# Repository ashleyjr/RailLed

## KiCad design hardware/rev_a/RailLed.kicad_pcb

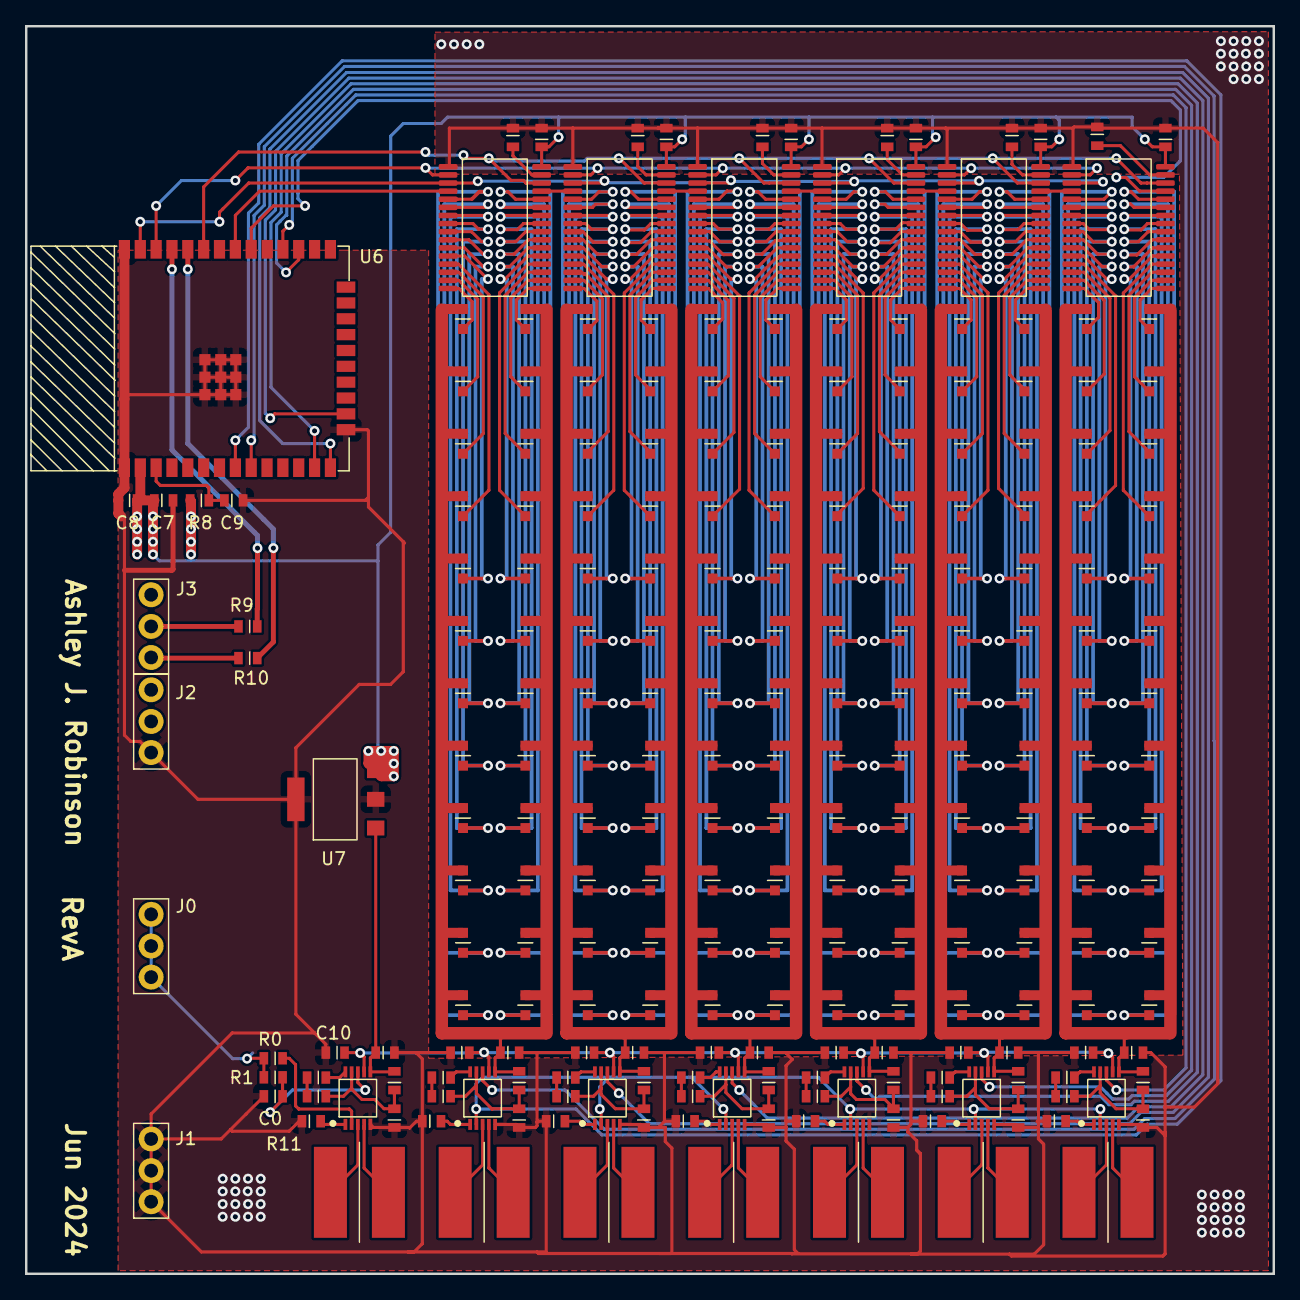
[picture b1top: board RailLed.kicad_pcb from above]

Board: 2 copper layers, 100.0 x 100.0 mm, 240 parts (0 on the bottom side), 226 nets.

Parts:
C0, C1, C2, C3, C4, C5, C6, C7, C8, C9, C10, C11, C12, C13, C14, C15, C16, C17, C18, C19, C20, C21, C22, C23, C24, C25, C26, C27, C28, C29, C30: CAP_0603; 0603
D0, D1, D2, D3, D4, D5, D6, D7, D8, D9, D10, D11, D12, D13, D14, D15, D16, D17, D18, D19, D20, D21, D22, D23, D24, D25, D26, D27, D28, D29, D30, D31, D32, D33, D34, D35, D36, D37, D38, D39, D40, D41, D42, D43, D44, D45, D46, D47, D48, D49, D50, D51, D52, D53, D54, D55, D56, D57, D58, D59, D60, D61, D62, D63, D64, D65, D66, D67, D68, D69, D70, D71, D72, D73, D74, D75, D76, D77, D78, D79, D80, D81, D82, D83, D84, D85, D86, D87, D88, D89, D90, D91, D92, D93, D94, D95, D96, D97, D98, D99, D100, D101, D102, D103, D104, D105, D106, D107, D108, D109, D110, D111, D112, D113, D114, D115, D116, D117, D118, D119, D120, D121, D122, D123, D124, D125, D126, D127, D128, D129, D130, D131, D132, D133, D134, D135, D136, D137, D138, D139, D140, D141, D142, D143: 150060GS75000
J0, J1, J2, J3: XG8V-0331
L0, L1, L2, L3, L4, L5, L6: CDRH6D38NP-100NC
R0, R1, R2, R3, R4, R5, R6, R7, R8, R9, R10, R11, R12, R13, R14, R15, R16, R17, R18, R19, R20, R21, R22, R23, R24, R25, R26, R27, R28, R29, R30, R31, R32, R33, R34, R35, R36, R37, R38: RES_0603; 0603
U0, U1, U2, U3, U4, U5: TLC5947DAP
U6: ESP32-WROOM-32D
U7: MIC5239-3.3YS
U8, U9, U10, U11, U12, U13, U14: LTC3440EMS#PBF

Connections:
+3V3: C1.1, C2.1, C3.1, C4.1, C5.1, C6.1, C7.1, C8.1, R8.2, U0.32 (VCC), U1.32 (VCC), U2.32 (VCC), U3.32 (VCC), U4.32 (VCC), U5.32 (VCC), U6.2 (3V3), U7.3 (OUT)
+BATT: C10.1, C13.1, C16.1, C19.1, C22.1, C25.1, C28.1, J0.1, J0.2, J0.3, R0.2, R1.2, U8.7 (Vin), U9.7 (Vin), U10.7 (Vin), U11.7 (Vin), U12.7 (Vin), U13.7 (Vin), U14.7 (Vin)
/BANK1/BLANK: U0.2 (BLANK), U1.2 (BLANK), U2.2 (BLANK), U3.2 (BLANK), U4.2 (BLANK), U5.2 (BLANK), U6.36 (IO22)
/BANK1/SCLK: U0.3 (SCLK), U1.3 (SCLK), U2.3 (SCLK), U3.3 (SCLK), U4.3 (SCLK), U5.3 (SCLK), U6.37 (IO23)
/BANK1/SIN: U0.4 (SIN), U6.31 (IO19)
/BANK1/SOUT: U0.29 (SOUT), U1.4 (SIN)
/BANK1/VLED: C15.1, D0.2, D1.2, D2.2, D3.2, D4.2, D5.2, D6.2, D7.2, D8.2, D9.2, D10.2, D11.2, D12.2, D13.2, D14.2, D15.2, D16.2, D17.2, D18.2, D19.2, D20.2, D21.2, D22.2, D23.2, R17.2, U9.6 (Vout)
/BANK1/XLAT: U0.30 (XLAT), U1.30 (XLAT), U2.30 (XLAT), U3.30 (XLAT), U4.30 (XLAT), U5.30 (XLAT), U6.33 (IO21)
/BANK2/SOUT: U1.29 (SOUT), U2.4 (SIN)
/BANK2/VLED: C18.1, D24.2, D25.2, D26.2, D27.2, D28.2, D29.2, D30.2, D31.2, D32.2, D33.2, D34.2, D35.2, D36.2, D37.2, D38.2, D39.2, D40.2, D41.2, D42.2, D43.2, D44.2, D45.2, D46.2, D47.2, R21.2, U10.6 (Vout)
/BANK3/SOUT: U2.29 (SOUT), U3.4 (SIN)
/BANK3/VLED: C21.1, D48.2, D49.2, D50.2, D51.2, D52.2, D53.2, D54.2, D55.2, D56.2, D57.2, D58.2, D59.2, D60.2, D61.2, D62.2, D63.2, D64.2, D65.2, D66.2, D67.2, D68.2, D69.2, D70.2, D71.2, R25.2, U11.6 (Vout)
/BANK4/SOUT: U3.29 (SOUT), U4.4 (SIN)
/BANK4/VLED: C24.1, D72.2, D73.2, D74.2, D75.2, D76.2, D77.2, D78.2, D79.2, D80.2, D81.2, D82.2, D83.2, D84.2, D85.2, D86.2, D87.2, D88.2, D89.2, D90.2, D91.2, D92.2, D93.2, D94.2, D95.2, R29.2, U12.6 (Vout)
/BANK5/SOUT: U4.29 (SOUT), U5.4 (SIN)
/BANK5/VLED: C27.1, D96.2, D97.2, D98.2, D99.2, D100.2, D101.2, D102.2, D103.2, D104.2, D105.2, D106.2, D107.2, D108.2, D109.2, D110.2, D111.2, D112.2, D113.2, D114.2, D115.2, D116.2, D117.2, D118.2, D119.2, R33.2, U13.6 (Vout)
/BANK6/SOUT: U5.29 (SOUT), U6.30 (IO18)
/BANK6/VLED: C30.1, D120.2, D121.2, D122.2, D123.2, D124.2, D125.2, D126.2, D127.2, D128.2, D129.2, D130.2, D131.2, D132.2, D133.2, D134.2, D135.2, D136.2, D137.2, D138.2, D139.2, D140.2, D141.2, D142.2, D143.2, R37.2, U14.6 (Vout)
/MCU0/RX: J3.2, R9.2
/MCU0/TX: J3.1, R10.2
/MCU0/VIN: C12.1, R13.2, U7.1 (IN), U8.6 (Vout)
/MODE: U6.8 (IO32), U9.2 (MODE/SYNC), U10.2 (MODE/SYNC), U11.2 (MODE/SYNC), U12.2 (MODE/SYNC), U13.2 (MODE/SYNC), U14.2 (MODE/SYNC)
/POWER0/MODE: R0.1, U8.2 (MODE/SYNC)
/POWER0/~SHDN: C0.1, R1.1, U8.8 (~SHDN/SS)
/~SHDN1: U6.9 (IO33), U9.8 (~SHDN/SS)
/~SHDN2: U6.14 (IO12), U10.8 (~SHDN/SS)
/~SHDN3: U6.16 (IO13), U11.8 (~SHDN/SS)
/~SHDN4: U6.13 (IO14), U12.8 (~SHDN/SS)
/~SHDN5: U6.27 (IO16), U13.8 (~SHDN/SS)
/~SHDN6: U6.28 (IO17), U14.8 (~SHDN/SS)
GND: C0.2, C1.2, C2.2, C3.2, C4.2, C5.2, C6.2, C7.2, C8.2, C9.2, C10.2, C12.2, C13.2, C15.2, C16.2, C18.2, C19.2, C21.2, C22.2, C24.2, C25.2, C27.2, C28.2, C30.2, J1.1, J1.2, J1.3, J2.1, R2.1, R3.1, R4.1, R5.1, R6.1, R7.1, R11.1, R14.1, R15.1, R18.1, R19.1, R22.1, R23.1, R26.1, R27.1, R30.1, R31.1, R34.1, R35.1, R38.1, U0.1 (GND), U1.1 (GND), U2.1 (GND), U3.1 (GND), U4.1 (GND), U5.1 (GND), U6.1 (GND1), U6.15 (GND2), U6.38 (GND3), U6.39 (P_GND), U7.2 (GND), U7.4 (GND), U8.5 (GND), U9.5 (GND), U10.5 (GND), U11.5 (GND), U12.5 (GND), U13.5 (GND), U14.5 (GND)
unnamed: C9.1, R8.1, U6.3 (EN)
unnamed: C11.1, U8.10 (Vc)
unnamed: C11.2, R12.2
unnamed: C14.1, U9.10 (Vc)
unnamed: C14.2, R16.2
unnamed: C17.1, U10.10 (Vc)
unnamed: C17.2, R20.2
unnamed: C20.1, U11.10 (Vc)
unnamed: C20.2, R24.2
unnamed: C23.1, U12.10 (Vc)
unnamed: C23.2, R28.2
unnamed: C26.1, U13.10 (Vc)
unnamed: C26.2, R32.2
unnamed: C29.1, U14.10 (Vc)
unnamed: C29.2, R36.2
unnamed: D0.1, U0.5 (OUT0)
unnamed: D1.1, U0.6 (OUT1)
unnamed: D2.1, U0.7 (OUT2)
unnamed: D3.1, U0.8 (OUT3)
unnamed: D4.1, U0.9 (OUT4)
unnamed: D5.1, U0.10 (OUT5)
unnamed: D6.1, U0.11 (OUT6)
unnamed: D7.1, U0.12 (OUT7)
unnamed: D8.1, U0.13 (OUT8)
unnamed: D9.1, U0.14 (OUT9)
unnamed: D10.1, U0.15 (OUT10)
unnamed: D11.1, U0.16 (OUT11)
unnamed: D12.1, U0.17 (OUT12)
unnamed: D13.1, U0.18 (OUT13)
unnamed: D14.1, U0.19 (OUT14)
unnamed: D15.1, U0.20 (OUT15)
unnamed: D16.1, U0.21 (OUT16)
unnamed: D17.1, U0.22 (OUT17)
unnamed: D18.1, U0.23 (OUT18)
unnamed: D19.1, U0.24 (OUT19)
unnamed: D20.1, U0.25 (OUT20)
unnamed: D21.1, U0.26 (OUT21)
unnamed: D22.1, U0.27 (OUT22)
unnamed: D23.1, U0.28 (OUT23)
unnamed: D24.1, U1.5 (OUT0)
unnamed: D25.1, U1.6 (OUT1)
unnamed: D26.1, U1.7 (OUT2)
unnamed: D27.1, U1.8 (OUT3)
unnamed: D28.1, U1.9 (OUT4)
unnamed: D29.1, U1.10 (OUT5)
unnamed: D30.1, U1.11 (OUT6)
unnamed: D31.1, U1.12 (OUT7)
unnamed: D32.1, U1.13 (OUT8)
unnamed: D33.1, U1.14 (OUT9)
unnamed: D34.1, U1.15 (OUT10)
unnamed: D35.1, U1.16 (OUT11)
unnamed: D36.1, U1.17 (OUT12)
unnamed: D37.1, U1.18 (OUT13)
unnamed: D38.1, U1.19 (OUT14)
unnamed: D39.1, U1.20 (OUT15)
unnamed: D40.1, U1.21 (OUT16)
unnamed: D41.1, U1.22 (OUT17)
unnamed: D42.1, U1.23 (OUT18)
unnamed: D43.1, U1.24 (OUT19)
unnamed: D44.1, U1.25 (OUT20)
unnamed: D45.1, U1.26 (OUT21)
unnamed: D46.1, U1.27 (OUT22)
unnamed: D47.1, U1.28 (OUT23)
unnamed: D48.1, U2.5 (OUT0)
unnamed: D49.1, U2.6 (OUT1)
unnamed: D50.1, U2.7 (OUT2)
unnamed: D51.1, U2.8 (OUT3)
unnamed: D52.1, U2.9 (OUT4)
unnamed: D53.1, U2.10 (OUT5)
unnamed: D54.1, U2.11 (OUT6)
unnamed: D55.1, U2.12 (OUT7)
unnamed: D56.1, U2.13 (OUT8)
unnamed: D57.1, U2.14 (OUT9)
unnamed: D58.1, U2.15 (OUT10)
unnamed: D59.1, U2.16 (OUT11)
unnamed: D60.1, U2.17 (OUT12)
unnamed: D61.1, U2.18 (OUT13)
unnamed: D62.1, U2.19 (OUT14)
unnamed: D63.1, U2.20 (OUT15)
unnamed: D64.1, U2.21 (OUT16)
unnamed: D65.1, U2.22 (OUT17)
unnamed: D66.1, U2.23 (OUT18)
unnamed: D67.1, U2.24 (OUT19)
unnamed: D68.1, U2.25 (OUT20)
unnamed: D69.1, U2.26 (OUT21)
unnamed: D70.1, U2.27 (OUT22)
unnamed: D71.1, U2.28 (OUT23)
unnamed: D72.1, U3.5 (OUT0)
unnamed: D73.1, U3.6 (OUT1)
unnamed: D74.1, U3.7 (OUT2)
unnamed: D75.1, U3.8 (OUT3)
unnamed: D76.1, U3.9 (OUT4)
unnamed: D77.1, U3.10 (OUT5)
unnamed: D78.1, U3.11 (OUT6)
unnamed: D79.1, U3.12 (OUT7)
unnamed: D80.1, U3.13 (OUT8)
unnamed: D81.1, U3.14 (OUT9)
unnamed: D82.1, U3.15 (OUT10)
unnamed: D83.1, U3.16 (OUT11)
unnamed: D84.1, U3.17 (OUT12)
unnamed: D85.1, U3.18 (OUT13)
unnamed: D86.1, U3.19 (OUT14)
unnamed: D87.1, U3.20 (OUT15)
unnamed: D88.1, U3.21 (OUT16)
unnamed: D89.1, U3.22 (OUT17)
unnamed: D90.1, U3.23 (OUT18)
unnamed: D91.1, U3.24 (OUT19)
unnamed: D92.1, U3.25 (OUT20)
unnamed: D93.1, U3.26 (OUT21)
unnamed: D94.1, U3.27 (OUT22)
unnamed: D95.1, U3.28 (OUT23)
unnamed: D96.1, U4.5 (OUT0)
unnamed: D97.1, U4.6 (OUT1)
unnamed: D98.1, U4.7 (OUT2)
unnamed: D99.1, U4.8 (OUT3)
unnamed: D100.1, U4.9 (OUT4)
unnamed: D101.1, U4.10 (OUT5)
unnamed: D102.1, U4.11 (OUT6)
unnamed: D103.1, U4.12 (OUT7)
unnamed: D104.1, U4.13 (OUT8)
unnamed: D105.1, U4.14 (OUT9)
unnamed: D106.1, U4.15 (OUT10)
unnamed: D107.1, U4.16 (OUT11)
unnamed: D108.1, U4.17 (OUT12)
unnamed: D109.1, U4.18 (OUT13)
unnamed: D110.1, U4.19 (OUT14)
unnamed: D111.1, U4.20 (OUT15)
unnamed: D112.1, U4.21 (OUT16)
unnamed: D113.1, U4.22 (OUT17)
unnamed: D114.1, U4.23 (OUT18)
unnamed: D115.1, U4.24 (OUT19)
unnamed: D116.1, U4.25 (OUT20)
unnamed: D117.1, U4.26 (OUT21)
unnamed: D118.1, U4.27 (OUT22)
unnamed: D119.1, U4.28 (OUT23)
unnamed: D120.1, U5.5 (OUT0)
unnamed: D121.1, U5.6 (OUT1)
unnamed: D122.1, U5.7 (OUT2)
unnamed: D123.1, U5.8 (OUT3)
unnamed: D124.1, U5.9 (OUT4)
unnamed: D125.1, U5.10 (OUT5)
unnamed: D126.1, U5.11 (OUT6)
unnamed: D127.1, U5.12 (OUT7)
unnamed: D128.1, U5.13 (OUT8)
unnamed: D129.1, U5.14 (OUT9)
unnamed: D130.1, U5.15 (OUT10)
unnamed: D131.1, U5.16 (OUT11)
unnamed: D132.1, U5.17 (OUT12)
unnamed: D133.1, U5.18 (OUT13)
unnamed: D134.1, U5.19 (OUT14)
unnamed: D135.1, U5.20 (OUT15)
unnamed: D136.1, U5.21 (OUT16)
unnamed: D137.1, U5.22 (OUT17)
unnamed: D138.1, U5.23 (OUT18)
unnamed: D139.1, U5.24 (OUT19)
unnamed: D140.1, U5.25 (OUT20)
unnamed: D141.1, U5.26 (OUT21)
unnamed: D142.1, U5.27 (OUT22)
unnamed: D143.1, U5.28 (OUT23)
unnamed: L0.1, U8.3 (SW1)
unnamed: L0.2, U8.4 (SW2)
unnamed: L1.1, U9.3 (SW1)
unnamed: L1.2, U9.4 (SW2)
unnamed: L2.1, U10.3 (SW1)
unnamed: L2.2, U10.4 (SW2)
unnamed: L3.1, U11.3 (SW1)
unnamed: L3.2, U11.4 (SW2)
unnamed: L4.1, U12.3 (SW1)
unnamed: L4.2, U12.4 (SW2)
unnamed: L5.1, U13.3 (SW1)
unnamed: L5.2, U13.4 (SW2)
unnamed: L6.1, U14.3 (SW1)
unnamed: L6.2, U14.4 (SW2)
unnamed: R2.2, U0.31 (IREF)
unnamed: R3.2, U1.31 (IREF)
unnamed: R4.2, U2.31 (IREF)
unnamed: R5.2, U3.31 (IREF)
unnamed: R6.2, U4.31 (IREF)
unnamed: R7.2, U5.31 (IREF)
unnamed: R9.1, U6.35 (TXDO)
unnamed: R10.1, U6.34 (RXD0)
unnamed: R11.2, U8.1 (Rt)
unnamed: R12.1, R13.1, R14.2, U8.9 (FB)
unnamed: R15.2, U9.1 (Rt)
unnamed: R16.1, R17.1, R18.2, U9.9 (FB)
unnamed: R19.2, U10.1 (Rt)
unnamed: R20.1, R21.1, R22.2, U10.9 (FB)
unnamed: R23.2, U11.1 (Rt)
unnamed: R24.1, R25.1, R26.2, U11.9 (FB)
unnamed: R27.2, U12.1 (Rt)
unnamed: R28.1, R29.1, R30.2, U12.9 (FB)
unnamed: R31.2, U13.1 (Rt)
unnamed: R32.1, R33.1, R34.2, U13.9 (FB)
unnamed: R35.2, U14.1 (Rt)
unnamed: R36.1, R37.1, R38.2, U14.9 (FB)

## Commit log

2024-06-09 Test IO
2024-06-09 Add hardware
2024-06-11 Fab out
2024-07-16 sw working on one ic
